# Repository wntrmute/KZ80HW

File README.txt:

WNTRMUTE HARDWARE

This is the electronic design around the KZ80 laptop.

+ KZ80: the actual laptop hardware.
+ tools: support hardware (e.g. programmers).
+ wntrmute.lbr: the WNTRMUTE hardware library.

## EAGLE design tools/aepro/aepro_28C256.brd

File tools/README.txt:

KZ80 tooling
============

This contains support hardware, such as programmers.

+ aepro: AVR EEPROM Programmer
  + 27C512 version
  + 28C256 version
+ busmon: Z80 bus monitor
+ eeprom_adapter: 28-pin wide DIL to ZIF adapter
  + adapter27: for 27C512
  + adapter28: for 28C256
+ m328pgm: ATmega328 programmer for use with AVRISP mkII
+ m1284pgm: ATmega1284 programmer for use with AVRISP mkII
+ RC2014_SIO2: RC2014-compatible SIO/2 board
  + This is built from the standard enhanced-bus SIO/2 board,
    but it only uses the standard (39-pin) RC2014 bus.
  + Note: clock speed is derived from the RC2014 bus, and must
    be 7.4 MHz for 115200 baud operation.
+ SIO2_dev: RC2014 SIO/2 converted to KZ80 interconnect.
+ sercon: standalone serial console

All designs except SIO2_dev are on order but are, as of yet, untested.

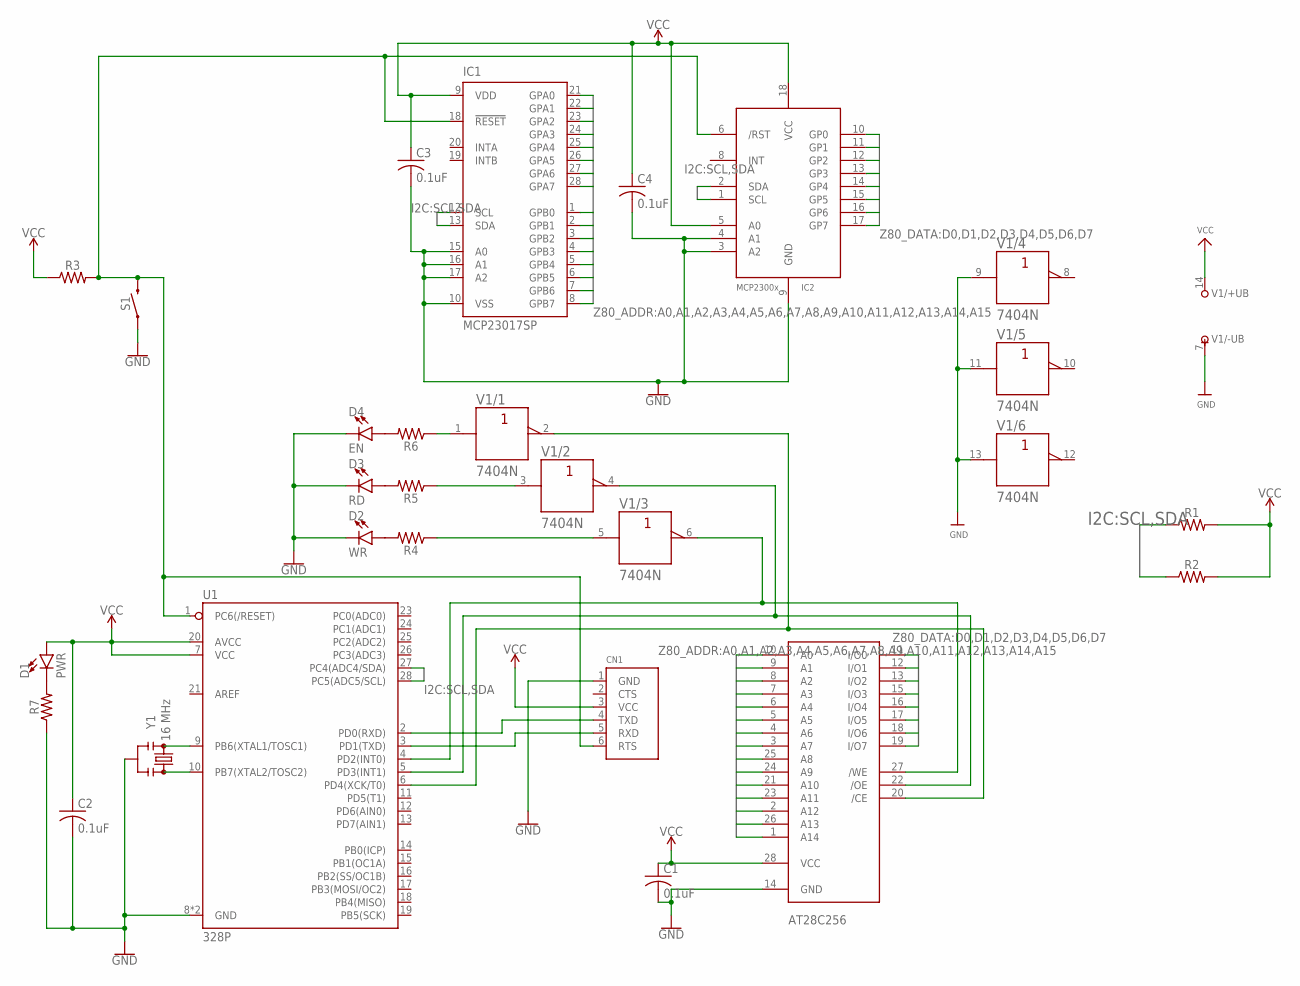
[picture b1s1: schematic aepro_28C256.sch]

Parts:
C1, C2, C3, C4: 0.1uF; C050-024X044
CN1: FTDIUSBCABLE; 1X06_ROUND
D1: PWR; LED_3MM
D2: WR; LED_3MM
D3: RD; LED_3MM
D4: EN; LED_3MM
IC1: MCP23017SP; DIL28-3
IC2: MCP23008/P; DIL18
R1, R2, R3, R4, R5, R6, R7: AXIAL-0.3
S1: MOMENTARY-SWITCH-SPST-PTH-6.0MM; TACTILE_SWITCH_PTH_6.0MM
U1: 328P; DIP28
U$1: AT28C256; DIL28-6-ZIF_SOCKET
V1: 7404N; DIL14
Y1: 16 MHz; RESONATOR-PTH-7.6X3.8

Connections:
A0: IC1.21 (GPA0), U$1.10 (A0)
A1: IC1.22 (GPA1), U$1.9 (A1)
A2: IC1.23 (GPA2), U$1.8 (A2)
A3: IC1.24 (GPA3), U$1.7 (A3)
A4: IC1.25 (GPA4), U$1.6 (A4)
A5: IC1.26 (GPA5), U$1.5 (A5)
A6: IC1.27 (GPA6), U$1.4 (A6)
A7: IC1.28 (GPA7), U$1.3 (A7)
A8: IC1.1 (GPB0), U$1.25 (A8)
A9: IC1.2 (GPB1), U$1.24 (A9)
A10: IC1.3 (GPB2), U$1.21 (A10)
A11: IC1.4 (GPB3), U$1.23 (A11)
A12: IC1.5 (GPB4), U$1.2 (A12)
A13: IC1.6 (GPB5), U$1.26 (A13)
A14: IC1.7 (GPB6), U$1.1 (A14)
A15: IC1.8 (GPB7)
CE: U1.6 (PD4(XCK/T0)), U$1.20 (/CE), V1.2 (Y)
D0: IC2.10 (GP0), U$1.11 (I/O0)
D1: IC2.11 (GP1), U$1.12 (I/O1)
D2: IC2.12 (GP2), U$1.13 (I/O2)
D3: IC2.13 (GP3), U$1.15 (I/O3)
D4: IC2.14 (GP4), U$1.16 (I/O4)
D5: IC2.15 (GP5), U$1.17 (I/O5)
D6: IC2.16 (GP6), U$1.18 (I/O6)
D7: IC2.17 (GP7), U$1.19 (I/O7)
GND: C1.2, C2.2, C3.2, C4.2, CN1.1 (GND), D2.K (C), D3.K (C), D4.K (C), IC1.10 (VSS), IC1.15 (A0), IC1.16 (A1), IC1.17 (A2), IC2.3 (A2), IC2.4 (A1), IC2.9 (GND), R7.P$1 (1), S1.1, U1.8 (GND), U1.22 (GND), U$1.14 (GND), V1.7 (-UB), V1.9 (A), V1.11 (A), V1.13 (A), Y1.2
unnamed: D2.A, R4.P$2 (2)
unnamed: R4.P$1 (1), V1.5 (A)
unnamed: CN1.5 (RXD), U1.3 (PD1(TXD))
unnamed: CN1.6 (RTS), IC1.18 (!RESET), IC2.6 (/RST), R3.P$2 (2), S1.3 (2), U1.1 (PC6(/RESET))
unnamed: D3.A, R5.P$2 (2)
unnamed: D4.A, R6.P$2 (2)
unnamed: D1.K (C), R7.P$2 (2)
unnamed: R5.P$1 (1), V1.3 (A)
unnamed: CN1.4 (TXD), U1.2 (PD0(RXD))
unnamed: U1.9 (PB6(XTAL1/TOSC1)), Y1.1
unnamed: U1.10 (PB7(XTAL2/TOSC2)), Y1.3
unnamed: R6.P$1 (1), V1.1 (A)
OE: U1.5 (PD3(INT1)), U$1.22 (/OE), V1.4 (Y)
SCL: IC1.12 (SCL), IC2.1 (SCL), R1.P$1 (1), U1.28 (PC5(ADC5/SCL))
SDA: IC1.13 (SDA), IC2.2 (SDA), R2.P$1 (1), U1.27 (PC4(ADC4/SDA))
VCC: C1.1, C2.1, C3.1, C4.1, CN1.3 (VCC), D1.A, IC1.9 (VDD), IC2.5 (A0), IC2.18 (VCC), R1.P$2 (2), R2.P$2 (2), R3.P$1 (1), U1.7 (VCC), U1.20 (AVCC), U$1.28 (VCC), V1.14 (+UB)
WE: U1.4 (PD2(INT0)), U$1.27 (/WE), V1.6 (Y)

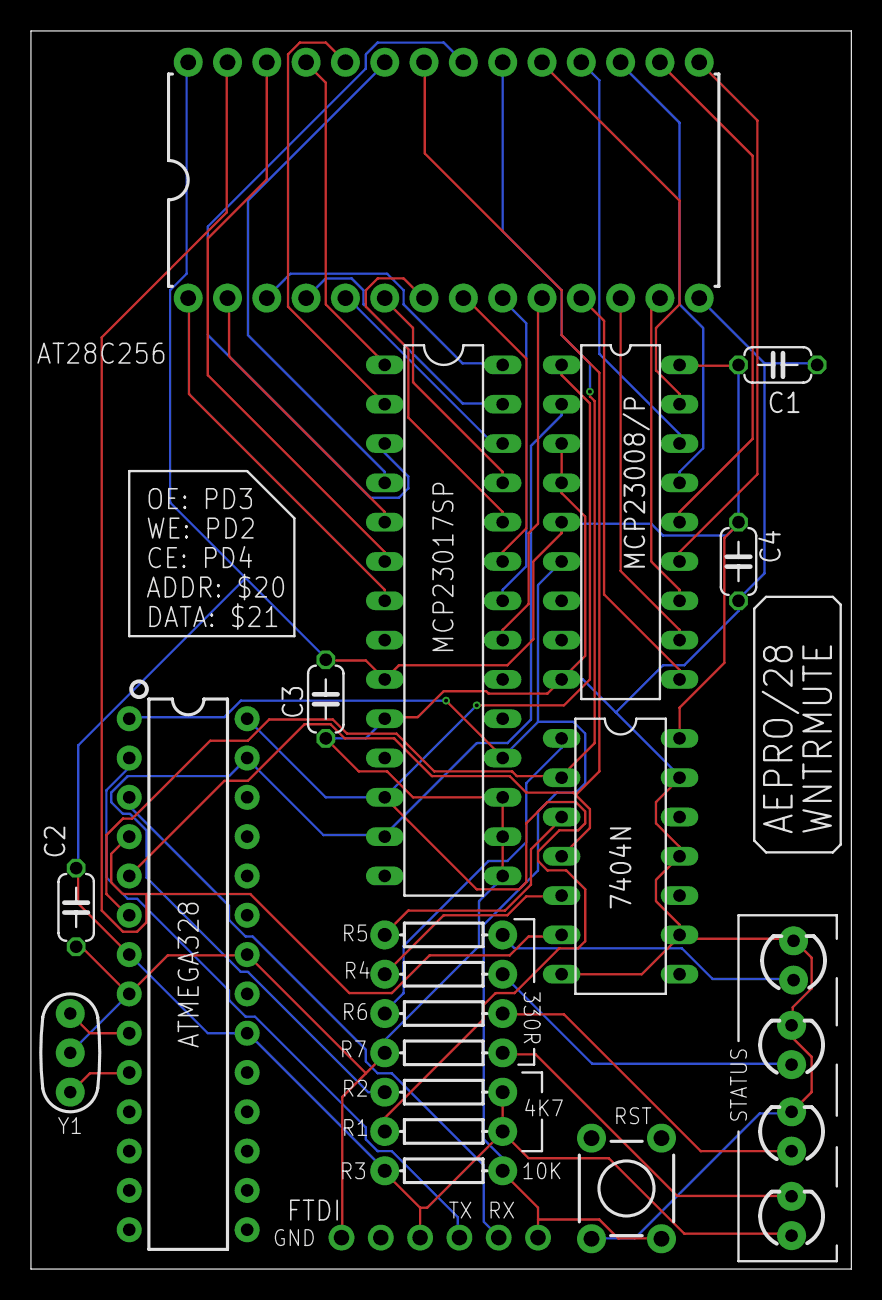
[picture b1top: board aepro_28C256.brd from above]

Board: 2 copper layers, 53.0 x 80.0 mm, 23 parts (0 on the bottom side), 42 nets.

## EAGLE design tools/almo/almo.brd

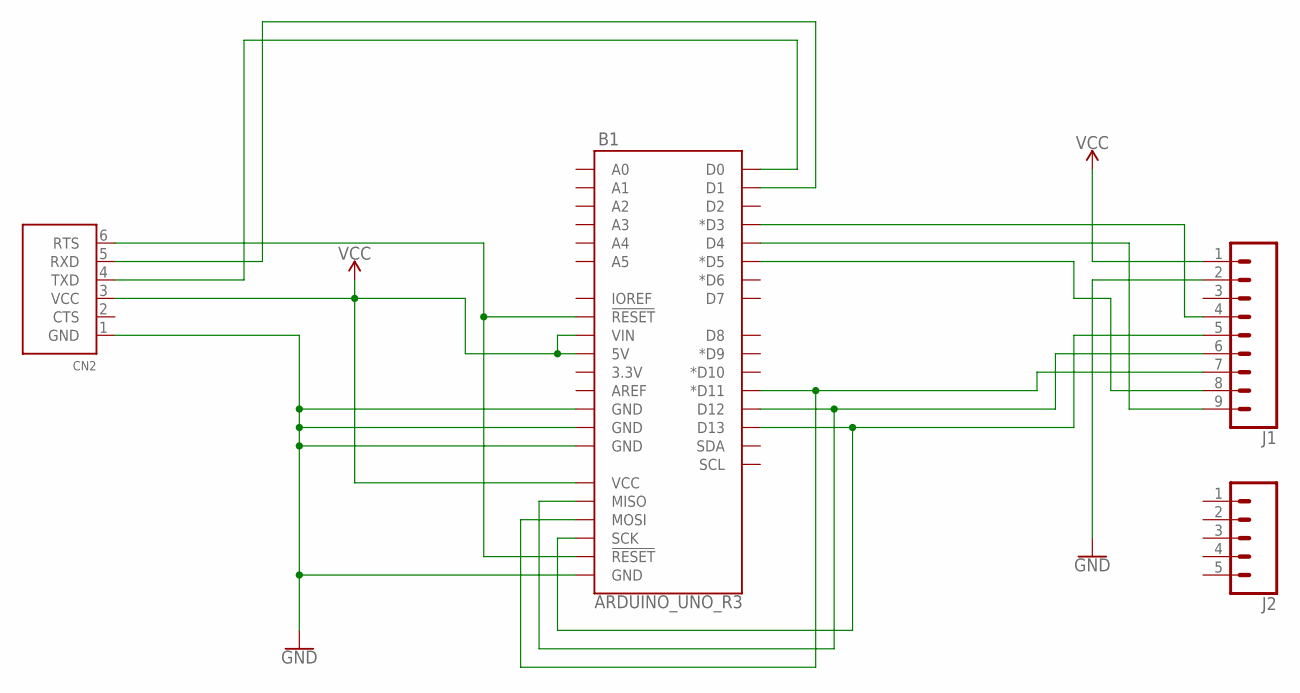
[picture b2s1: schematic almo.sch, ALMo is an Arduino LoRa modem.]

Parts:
B1: ARDUINO_UNO_R3; ARDUINO_R3
CN2: FTDIUSBCABLE; 1X06_ROUND
J1: CONN_09; 1X09
J2: CONN_05; 1X05

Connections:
GND: B1.GND@1 (GND), B1.GND@2 (GND), B1.GND@3 (GND), B1.GND@4 (GND), CN2.1 (GND), J1.2
unnamed: B1.D13, B1.SCK, J1.5
unnamed: B1.RESET@1 (!RESET!), B1.RESET@2 (!RESET!), CN2.6 (RTS)
unnamed: B1.D1, CN2.5 (RXD)
unnamed: B1.D0, CN2.4 (TXD)
unnamed: B1.D12, B1.MISO, J1.6
unnamed: B1.D11 (*D11), B1.MOSI, J1.7
unnamed: B1.D5 (*D5), J1.8
unnamed: B1.D4, J1.9
unnamed: B1.D3 (*D3), J1.4
VCC: B1.5V, B1.VCC, B1.VIN, CN2.3 (VCC), J1.1

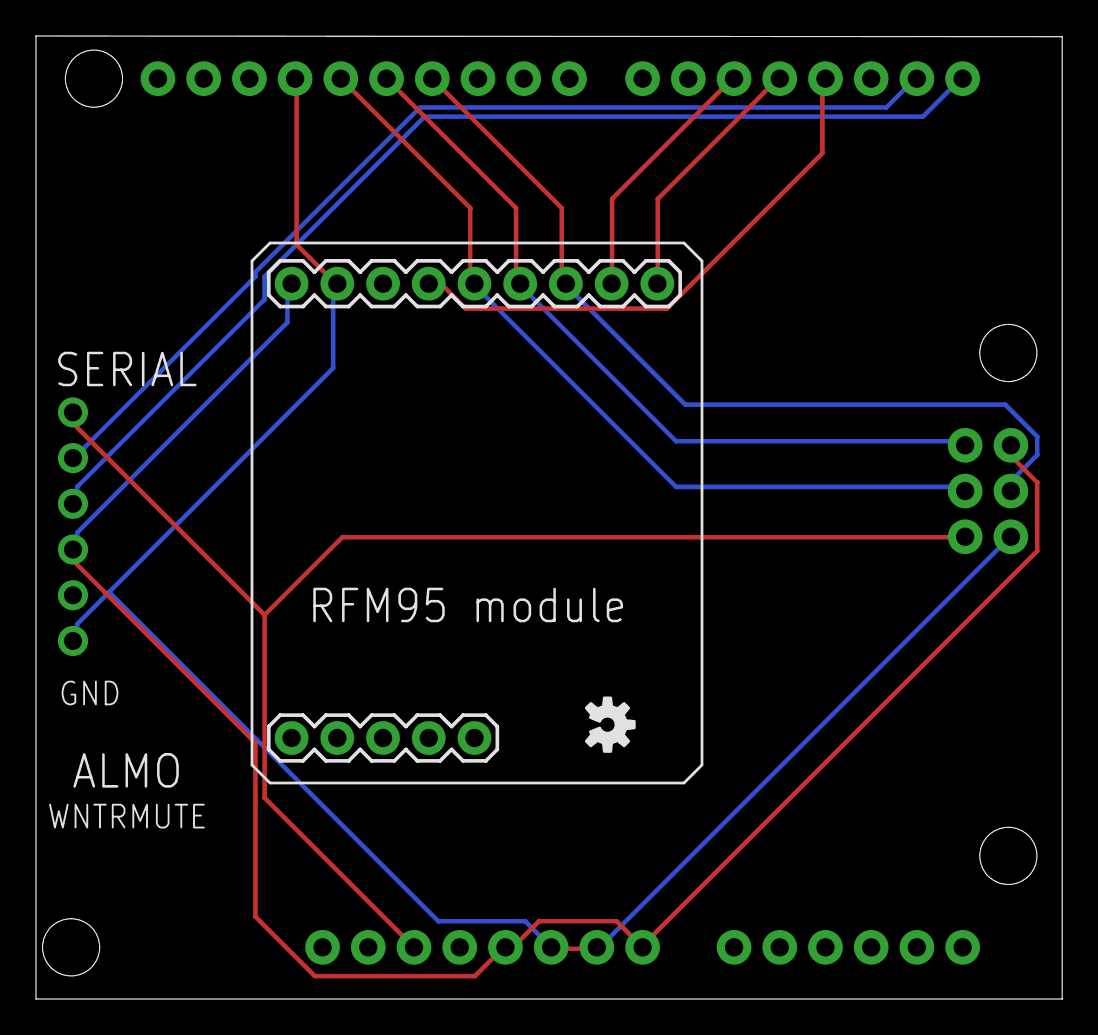
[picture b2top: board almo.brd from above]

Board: 2 copper layers, 57.0 x 53.5 mm, 5 parts (0 on the bottom side), 11 nets.

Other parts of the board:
U$1: OSHW-LOGO-S

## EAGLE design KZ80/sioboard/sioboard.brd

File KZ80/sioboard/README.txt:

SIO/2-based serial console
==========================

This is based on the RC2014 SIO/2 board from Spencer Owens [1]. It's
been adapted specifically to mount on top of the KZ80 mainboard.

|======+=========|
| Port | Address |
|======+=========|
| A/C  |     $80 |
|------+---------|
| A/D  |     $81 |
|------+---------|
| B/C  |     $82 |
|------+---------|
| B/D  |     $83 |
|------+---------|

A = SIO A
B = SIO B
C = CONTROL
D = DATA

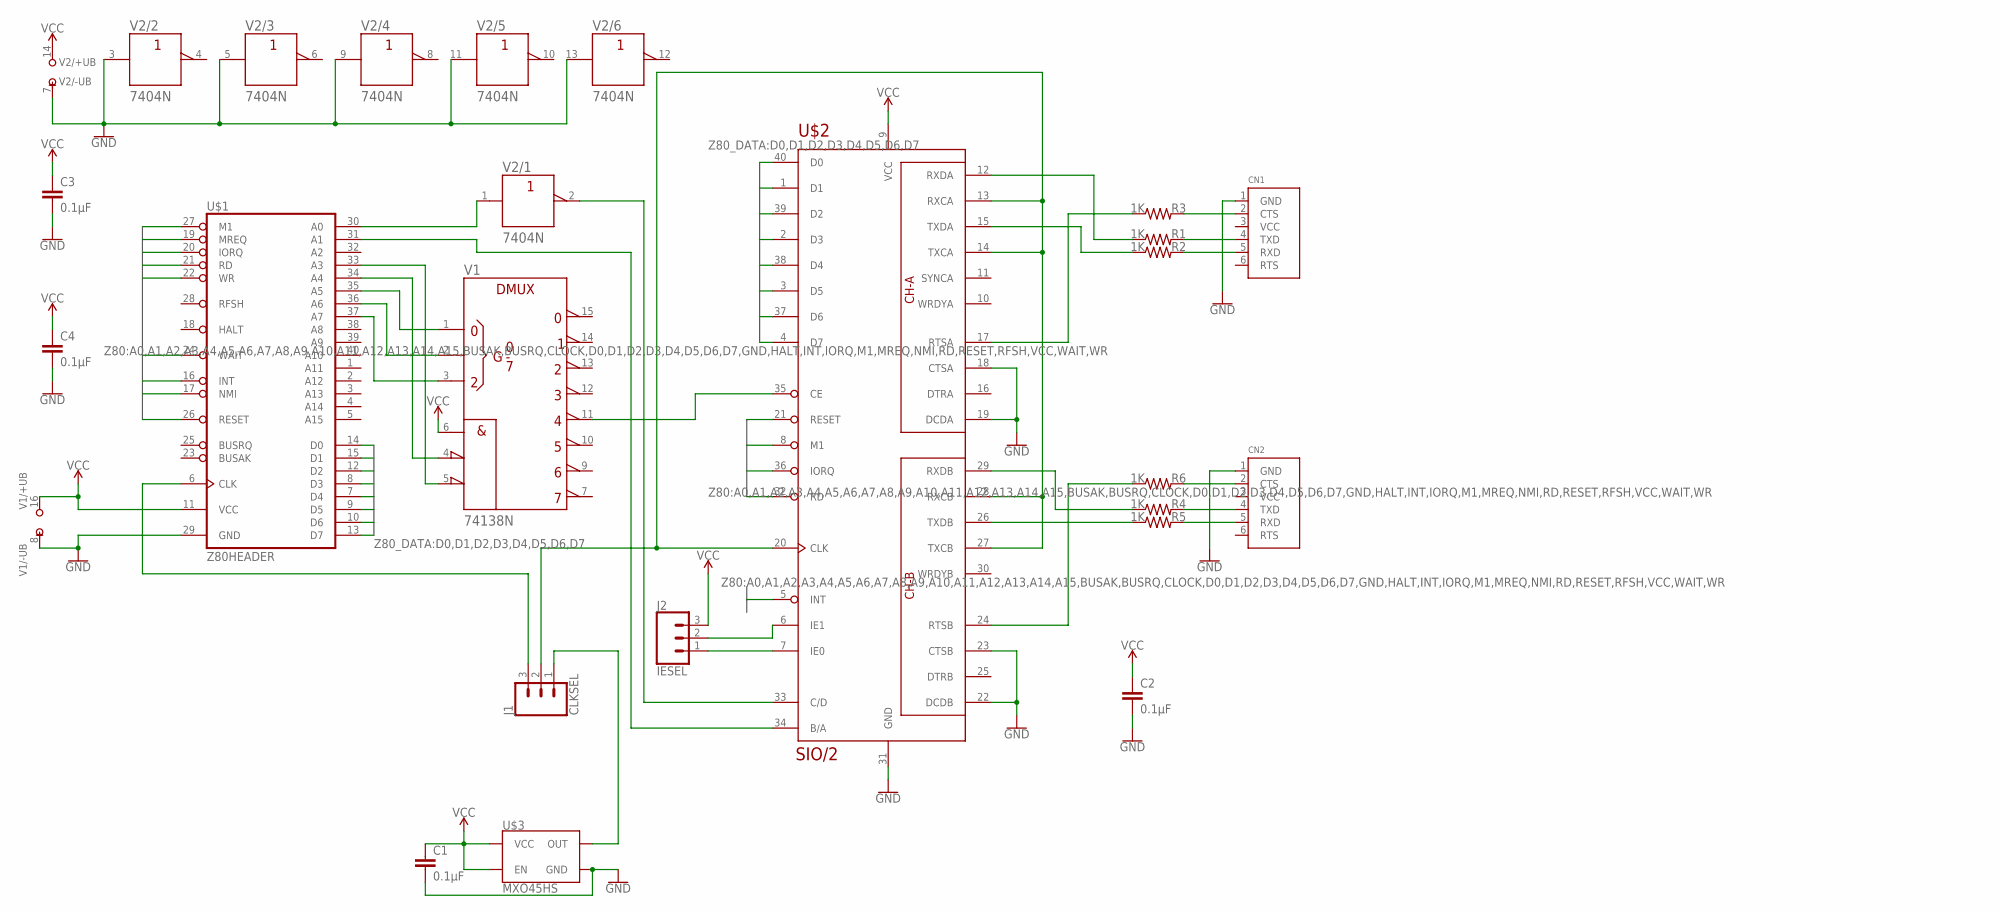
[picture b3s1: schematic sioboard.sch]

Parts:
C1, C2, C3, C4: 0.1µF; C2.5-3
CN1, CN2: FTDIUSBCABLE; 1X06_ROUND
J1: CLKSEL; 1X03
J2: IESEL; 1X03
R1, R2, R3, R4, R5, R6: 1K; AXIAL-0.3
U$1: Z80HEADER; 2X20
U$2: SIO/2; DIL40
U$3: MXO45HS; DIL08-HALF
V1: 74138N; DIL16
V2: 7404N; DIL14

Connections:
D0: U$1.14 (D0), U$2.40 (D0)
D1: U$1.15 (D1), U$2.1 (D1)
D2: U$1.12 (D2), U$2.39 (D2)
D3: U$1.8 (D3), U$2.2 (D3)
D4: U$1.7 (D4), U$2.38 (D4)
D5: U$1.9 (D5), U$2.3 (D5)
D6: U$1.10 (D6), U$2.37 (D6)
D7: U$1.13 (D7), U$2.4 (D7)
GND: C1.2, C2.2, C3.2, C4.2, CN1.1 (GND), CN2.1 (GND), U$1.29 (GND), U$2.18 (CTSA), U$2.19 (DCDA), U$2.22 (DCDB), U$2.23 (CTSB), U$2.31 (GND), U$3.4 (GND), V1.8 (-UB), V2.3 (A), V2.5 (A), V2.7 (-UB), V2.9 (A), V2.11 (A), V2.13 (A)
INT: U$1.16 (INT), U$2.5 (INT)
IORQ: U$1.20 (IORQ), U$2.36 (IORQ)
M1: U$1.27 (M1), U$2.8 (M1)
MREQ: U$1.19 (MREQ)
unnamed: J1.1, U$3.5 (OUT)
unnamed: J1.2, U$2.13 (RXCA), U$2.14 (TXCA), U$2.20 (CLK), U$2.27 (TXCB), U$2.28 (RXCB)
unnamed: J1.3, U$1.6 (CLK)
unnamed: U$1.37 (A7), V1.3 (C)
unnamed: U$1.36 (A6), V1.2 (B)
unnamed: U$1.35 (A5), V1.1 (A)
unnamed: U$1.34 (A4), V1.4 (!G2A)
unnamed: U$1.33 (A3), V1.5 (!G2B)
unnamed: U$2.35 (CE), V1.11 (Y4)
unnamed: U$1.31 (A1), U$2.34 (B/A)
unnamed: U$1.30 (A0), V2.1 (A)
unnamed: U$2.33 (C/D), V2.2 (Y)
unnamed: CN1.2 (CTS), R3.P$2 (2)
unnamed: CN1.4 (TXD), R1.P$2 (2)
unnamed: CN1.5 (RXD), R2.P$2 (2)
unnamed: R2.P$1 (1), U$2.15 (TXDA)
unnamed: R1.P$1 (1), U$2.12 (RXDA)
unnamed: R3.P$1 (1), U$2.17 (RTSA)
unnamed: R4.P$1 (1), U$2.29 (RXDB)
unnamed: R5.P$1 (1), U$2.26 (TXDB)
unnamed: CN2.5 (RXD), R5.P$2 (2)
unnamed: CN2.4 (TXD), R4.P$2 (2)
unnamed: R6.P$1 (1), U$2.24 (RTSB)
unnamed: CN2.2 (CTS), R6.P$2 (2)
unnamed: J2.1, U$2.7 (IE0)
unnamed: J2.2, U$2.6 (IE1)
NMI: U$1.17 (NMI)
RD: U$1.21 (RD), U$2.32 (RD)
RESET: U$1.26 (RESET), U$2.21 (RESET)
VCC: C1.1, C2.1, C3.1, C4.1, J2.3, U$1.11 (VCC), U$2.9 (VCC), U$3.1 (EN), U$3.8 (VCC), V1.6 (G1), V1.16 (+UB), V2.14 (+UB)
WAIT: U$1.24 (WAIT)
WR: U$1.22 (WR)

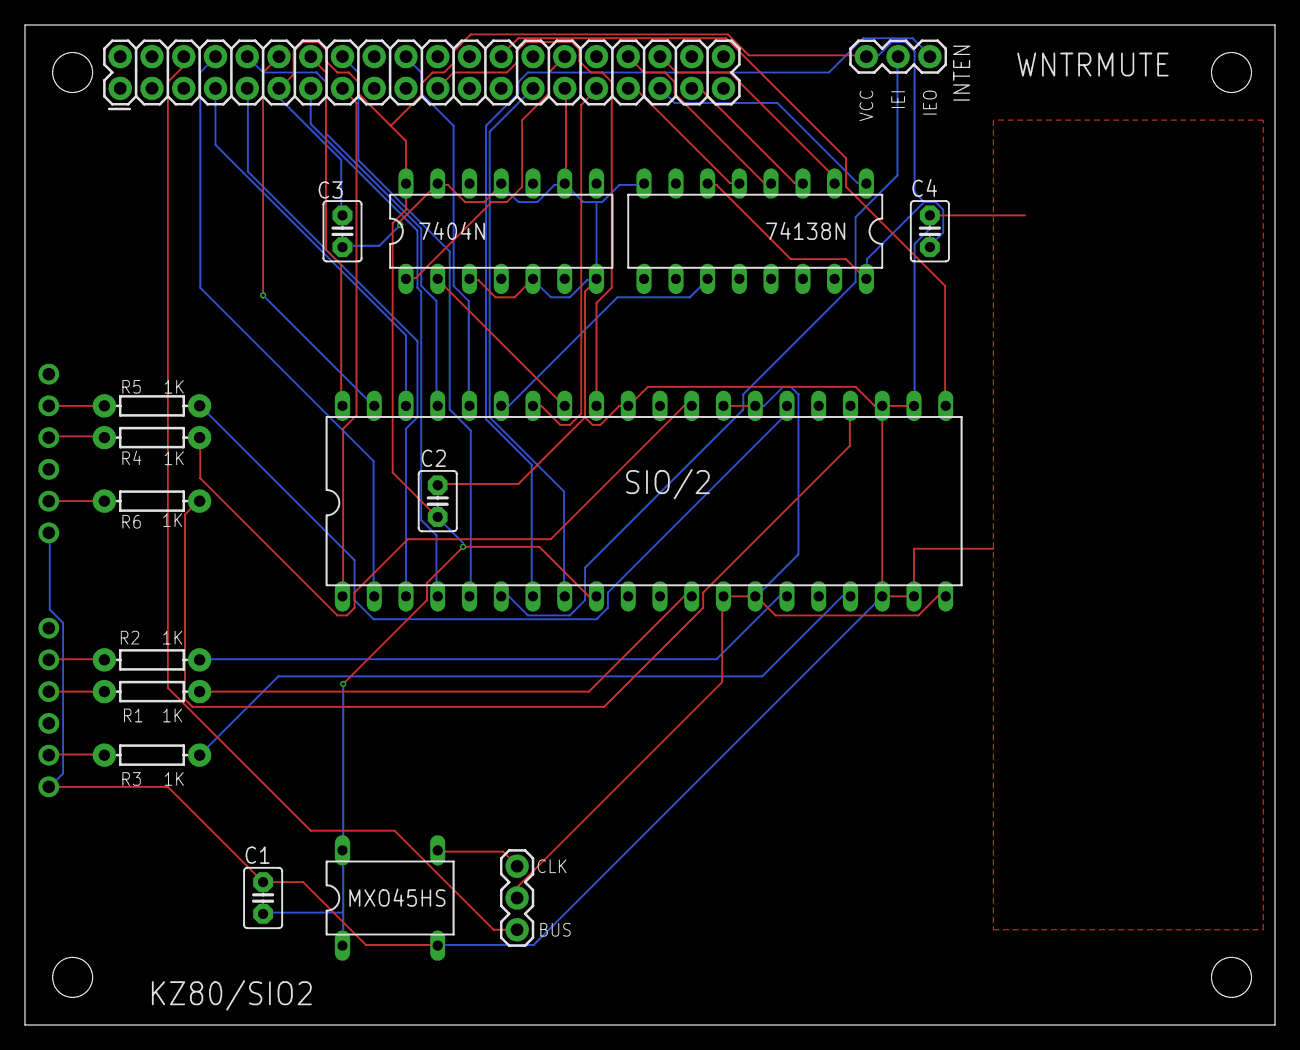
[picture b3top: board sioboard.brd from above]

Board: 2 copper layers, 100.0 x 80.0 mm, 19 parts (0 on the bottom side), 41 nets.

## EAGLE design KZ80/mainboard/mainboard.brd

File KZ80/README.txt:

KZ80 Designs
============

This is the actual KZ80 hardware.

+ backplane: KZ80 interconnect to 5-slot RC2014 bus.
+ mainboard: the current mainboard has 2x CY62256 32K RAM modules and an
  AT28C256 ROM. The ROM is attached to the lower 8K of the address space.
  This design does not feature paging out of the ROM, and as such is
  unsuitable for CP/M.
+ power: the power board provides the clock, a clock+5V connection to
  the mainboard, and a 3.3/5V connection to the I/O board.
+ sioboard: dual serial via a SIO/2.

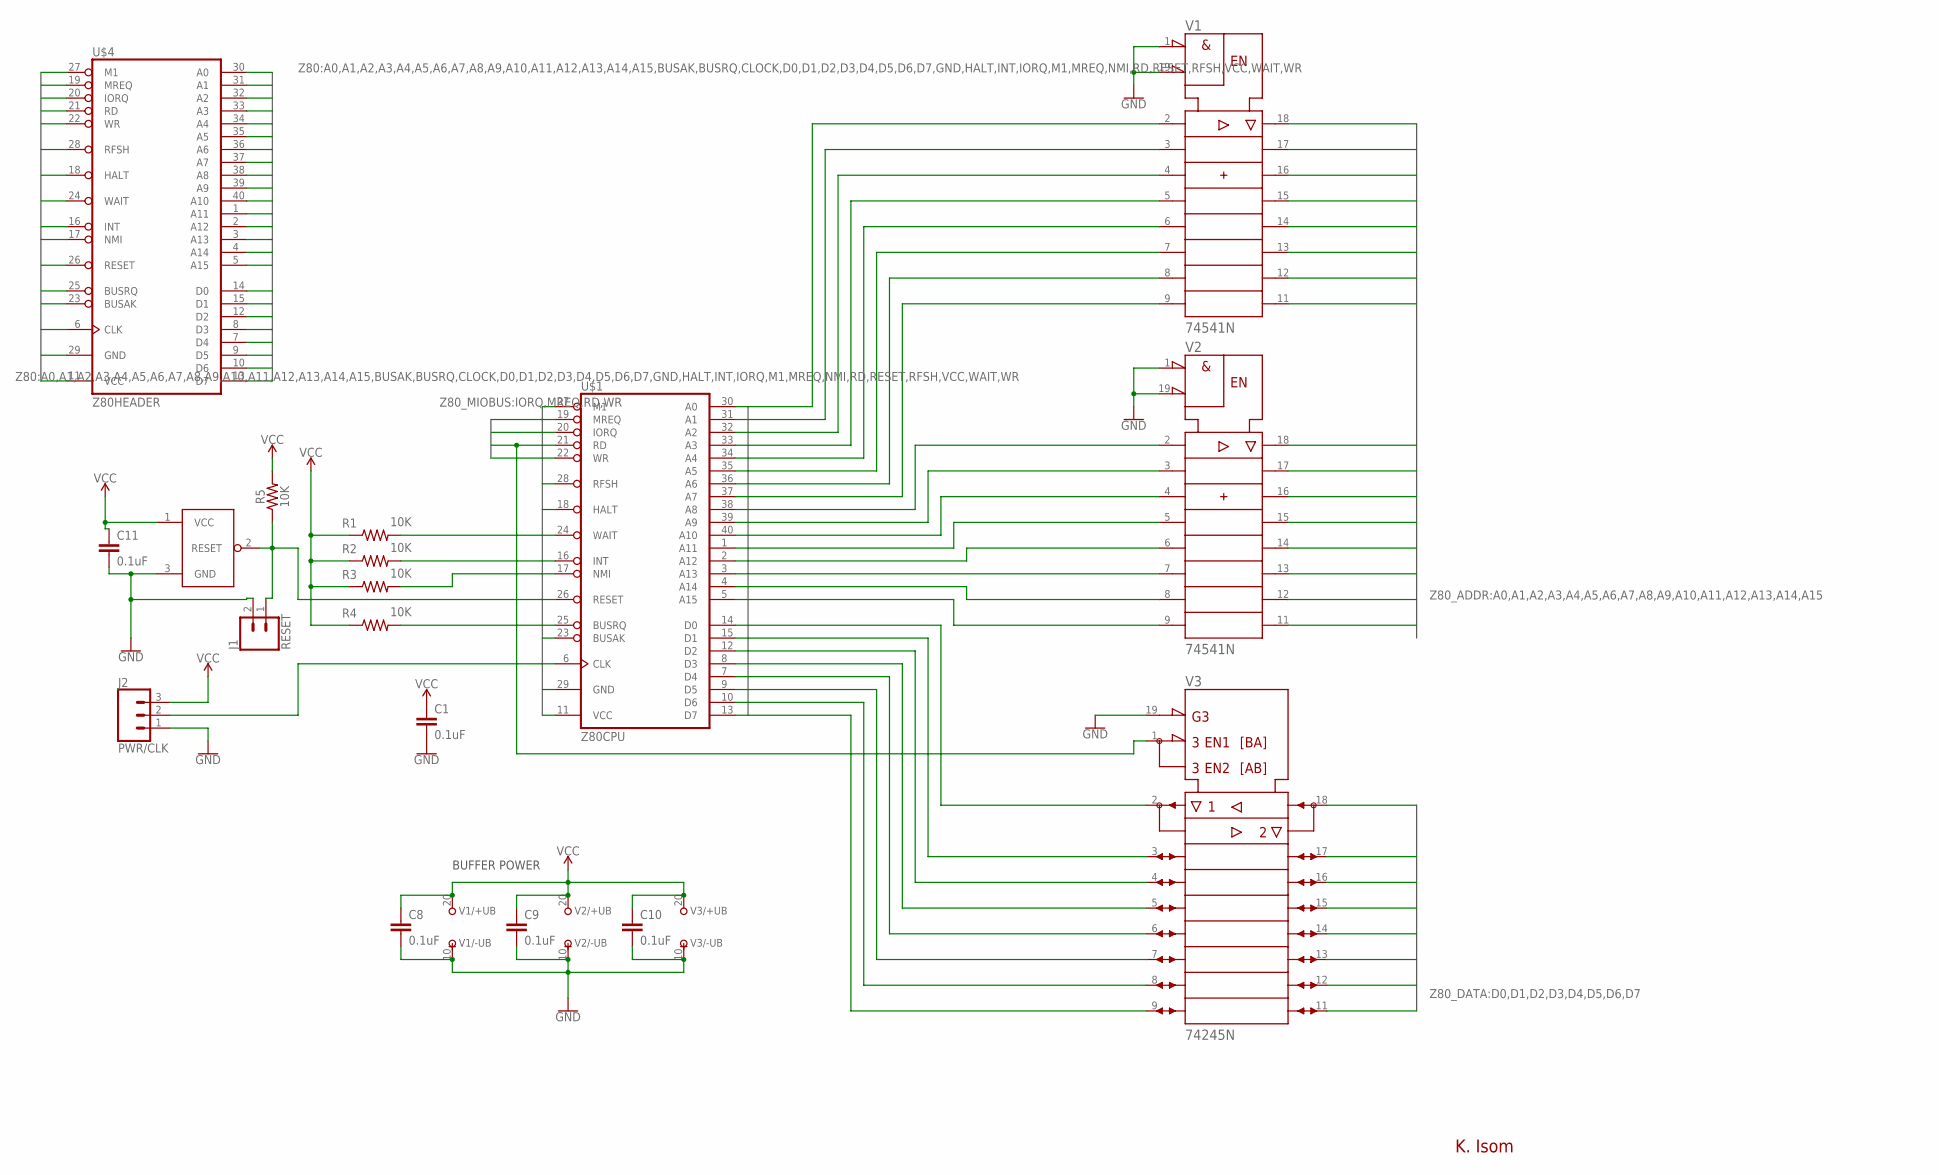
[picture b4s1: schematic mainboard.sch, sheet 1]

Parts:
C1, C8, C9, C10, C11: 0.1uF; C2.5-3
J1: RESET; 1X02
J2: PWR/CLK; SCREWTERMINAL-5MM-3
R1, R2, R3, R4, R5: 10K; AXIAL-0.3
U$1: Z80CPU; DIL40
U$2: MCP120/MCP130; TO-92-AMMO
U$4: Z80HEADER; 2X20
V1, V2: 74541N; DIL20
V3: 74245N; DIL20

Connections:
A0: U$1.30 (A0), U$4.30 (A0), V1.2 (A1), V1.18 (Y1); also elsewhere on the board
A1: U$1.31 (A1), U$4.31 (A1), V1.3 (A2), V1.17 (Y2); also elsewhere on the board
A2: U$1.32 (A2), U$4.32 (A2), V1.4 (A3), V1.16 (Y3); also elsewhere on the board
A3: U$1.33 (A3), U$4.33 (A3), V1.5 (A4), V1.15 (Y4); also elsewhere on the board
A4: U$1.34 (A4), U$4.34 (A4), V1.6 (A5), V1.14 (Y5); also elsewhere on the board
A5: U$1.35 (A5), U$4.35 (A5), V1.7 (A6), V1.13 (Y6); also elsewhere on the board
A6: U$1.36 (A6), U$4.36 (A6), V1.8 (A7), V1.12 (Y7); also elsewhere on the board
A7: U$1.37 (A7), U$4.37 (A7), V1.9 (A8), V1.11 (Y8); also elsewhere on the board
A8: U$1.38 (A8), U$4.38 (A8), V2.2 (A1), V2.18 (Y1); also elsewhere on the board
A9: U$1.39 (A9), U$4.39 (A9), V2.3 (A2), V2.17 (Y2); also elsewhere on the board
A10: U$1.40 (A10), U$4.40 (A10), V2.4 (A3), V2.16 (Y3); also elsewhere on the board
A11: U$1.1 (A11), U$4.1 (A11), V2.5 (A4), V2.15 (Y4); also elsewhere on the board
A12: U$1.2 (A12), U$4.2 (A12), V2.6 (A5), V2.14 (Y5); also elsewhere on the board
A13: U$1.3 (A13), U$4.3 (A13), V2.7 (A6), V2.13 (Y6); also elsewhere on the board
A14: U$1.4 (A14), U$4.4 (A14), V2.8 (A7), V2.12 (Y7); also elsewhere on the board
A15: U$1.5 (A15), U$4.5 (A15), V2.9 (A8), V2.11 (Y8); also elsewhere on the board
BUSAK: U$1.23 (BUSAK), U$4.23 (BUSAK)
BUSRQ: R4.P$2 (2), U$1.25 (BUSRQ), U$4.25 (BUSRQ)
CLOCK: J2.2, U$1.6 (CLK), U$4.6 (CLK)
D0: U$1.14 (D0), U$4.14 (D0), V3.2 (A1), V3.18 (B1); also elsewhere on the board
D1: U$1.15 (D1), U$4.15 (D1), V3.3 (A2), V3.17 (B2); also elsewhere on the board
D2: U$1.12 (D2), U$4.12 (D2), V3.4 (A3), V3.16 (B3); also elsewhere on the board
D3: U$1.8 (D3), U$4.8 (D3), V3.5 (A4), V3.15 (B4); also elsewhere on the board
D4: U$1.7 (D4), U$4.7 (D4), V3.6 (A5), V3.14 (B5); also elsewhere on the board
D5: U$1.9 (D5), U$4.9 (D5), V3.7 (A6), V3.13 (B6); also elsewhere on the board
D6: U$1.10 (D6), U$4.10 (D6), V3.8 (A7), V3.12 (B7); also elsewhere on the board
D7: U$1.13 (D7), U$4.13 (D7), V3.9 (A8), V3.11 (B8); also elsewhere on the board
GND: C1.2, C8.2, C9.2, C10.2, C11.2, J1.2, J2.1, U$1.29 (GND), U$2.3 (GND), U$4.29 (GND), V1.1 (!G1), V1.10 (-UB), V1.19 (!G2), V2.1 (!G1), V2.10 (-UB), V2.19 (!G2), V3.10 (-UB), V3.19 (!G); also elsewhere on the board
HALT: U$1.18 (HALT), U$4.18 (HALT)
INT: R2.P$2 (2), U$1.16 (INT), U$4.16 (INT)
IORQ: U$1.20 (IORQ), U$4.20 (IORQ)
M1: U$1.27 (M1), U$4.27 (M1)
MREQ: U$1.19 (MREQ), U$4.19 (MREQ); also elsewhere on the board
NMI: R3.P$2 (2), U$1.17 (NMI), U$4.17 (NMI)
RD: U$1.21 (RD), U$4.21 (RD), V3.1 (DIR); also elsewhere on the board
RESET: J1.1, R5.P$1 (1), U$1.26 (RESET), U$2.2 (RESET), U$4.26 (RESET)
RFSH: U$1.28 (RFSH), U$4.28 (RFSH)
VCC: C1.1, C8.1, C9.1, C10.1, C11.1, J2.3, R1.P$1 (1), R2.P$1 (1), R3.P$1 (1), R4.P$1 (1), R5.P$2 (2), U$1.11 (VCC), U$2.1 (VCC), U$4.11 (VCC), V1.20 (+UB), V2.20 (+UB), V3.20 (+UB); also elsewhere on the board
WAIT: R1.P$2 (2), U$1.24 (WAIT), U$4.24 (WAIT)
WR: U$1.22 (WR), U$4.22 (WR); also elsewhere on the board

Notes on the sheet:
K. Isom
BUFFER POWER

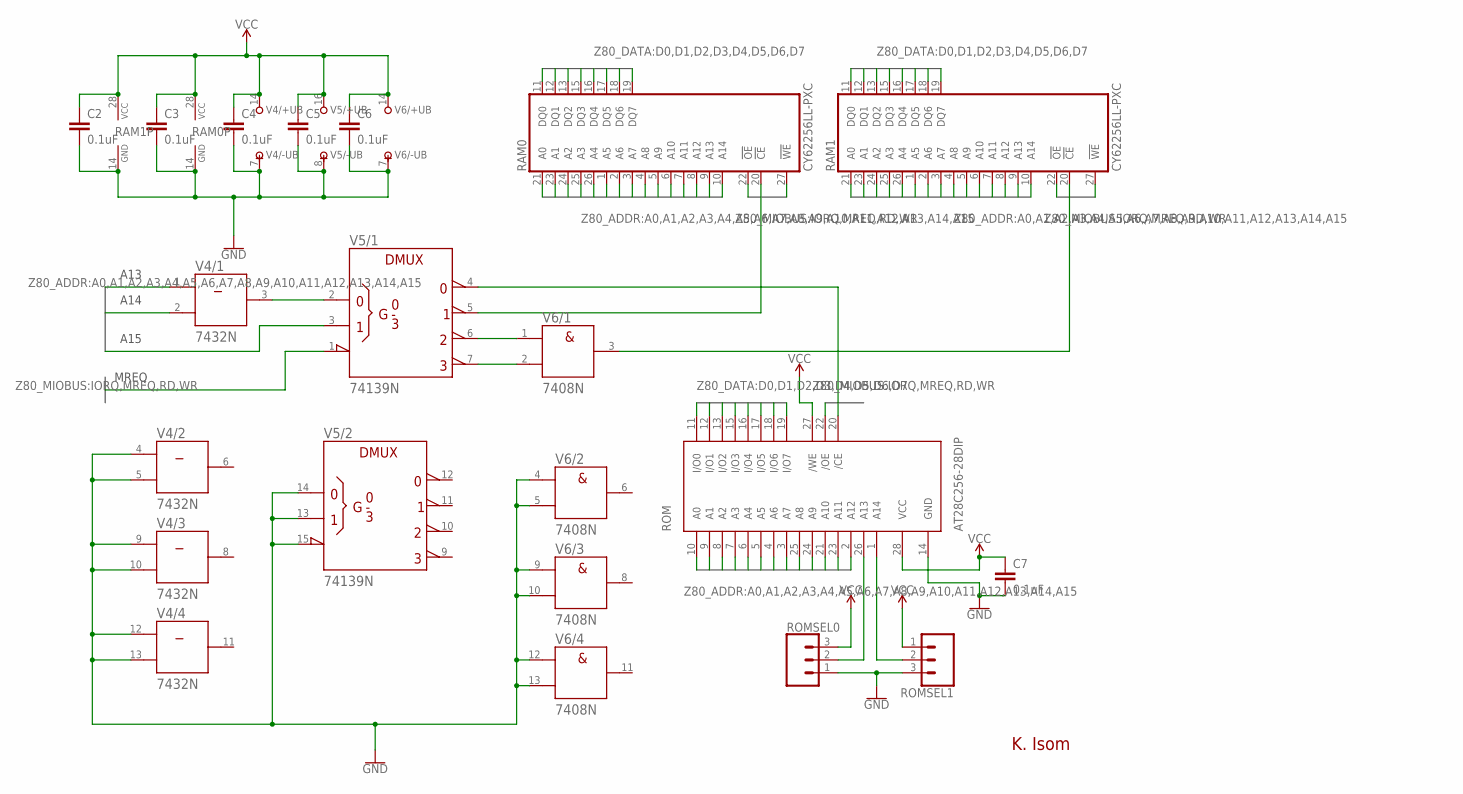
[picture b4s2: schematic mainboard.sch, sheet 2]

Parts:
C2, C3, C4, C5, C6, C7: 0.1uF; C2.5-3
RAM0, RAM1: CY62256LL-PXC; DIL28-6
ROM: AT28C256-28DIP; DIL28-6
ROMSEL0, ROMSEL1: 455-1750-1-ND; 1X03
V4: 7432N; DIL14
V5: 74139N; DIL16
V6: 7408N; DIL14

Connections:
A0: RAM0.21 (A0), RAM1.21 (A0), ROM.10 (A0); also elsewhere on the board
A1: RAM0.23 (A1), RAM1.23 (A1), ROM.9 (A1); also elsewhere on the board
A2: RAM0.24 (A2), RAM1.24 (A2), ROM.8 (A2); also elsewhere on the board
A3: RAM0.25 (A3), RAM1.25 (A3), ROM.7 (A3); also elsewhere on the board
A4: RAM0.26 (A4), RAM1.26 (A4), ROM.6 (A4); also elsewhere on the board
A5: RAM0.1 (A5), RAM1.1 (A5), ROM.5 (A5); also elsewhere on the board
A6: RAM0.2 (A6), RAM1.2 (A6), ROM.4 (A6); also elsewhere on the board
A7: RAM0.3 (A7), RAM1.3 (A7), ROM.3 (A7); also elsewhere on the board
A8: RAM0.4 (A8), RAM1.4 (A8), ROM.25 (A8); also elsewhere on the board
A9: RAM0.5 (A9), RAM1.5 (A9), ROM.24 (A9); also elsewhere on the board
A10: RAM0.6 (A10), RAM1.6 (A10), ROM.21 (A10); also elsewhere on the board
A11: RAM0.7 (A11), RAM1.7 (A11), ROM.23 (A11); also elsewhere on the board
A12: RAM0.8 (A12), RAM1.8 (A12), ROM.2 (A12); also elsewhere on the board
A13: RAM0.9 (A13), RAM1.9 (A13), V4.1 (A); also elsewhere on the board
A14: RAM0.10 (A14), RAM1.10 (A14), V4.2 (B); also elsewhere on the board
A15: V5.3 (B); also elsewhere on the board
D0: RAM0.11 (DQ0), RAM1.11 (DQ0), ROM.11 (I/O0); also elsewhere on the board
D1: RAM0.12 (DQ1), RAM1.12 (DQ1), ROM.12 (I/O1); also elsewhere on the board
D2: RAM0.13 (DQ2), RAM1.13 (DQ2), ROM.13 (I/O2); also elsewhere on the board
D3: RAM0.15 (DQ3), RAM1.15 (DQ3), ROM.15 (I/O3); also elsewhere on the board
D4: RAM0.16 (DQ4), RAM1.16 (DQ4), ROM.16 (I/O4); also elsewhere on the board
D5: RAM0.17 (DQ5), RAM1.17 (DQ5), ROM.17 (I/O5); also elsewhere on the board
D6: RAM0.18 (DQ6), RAM1.18 (DQ6), ROM.18 (I/O6); also elsewhere on the board
D7: RAM0.19 (DQ7), RAM1.19 (DQ7), ROM.19 (I/O7); also elsewhere on the board
GND: C2.2, C3.2, C4.2, C5.2, C6.2, C7.2, RAM0.14 (GND), RAM1.14 (GND), ROM.14 (GND), ROMSEL0.1, ROMSEL1.3, V4.4 (A), V4.5 (B), V4.7 (-UB), V4.9 (A), V4.10 (B), V4.12 (A), V4.13 (B), V5.8 (-UB), V5.13 (B), V5.14 (A), V5.15 (!G), V6.4 (A), V6.5 (B), V6.7 (-UB), V6.9 (A), V6.10 (B), V6.12 (A), V6.13 (B); also elsewhere on the board
MREQ: V5.1 (!G); also elsewhere on the board
unnamed: ROM.26 (A13), ROMSEL0.2
unnamed: V4.3 (Y), V5.2 (A)
unnamed: V5.6 (Y2), V6.1 (A)
unnamed: V5.7 (Y3), V6.2 (B)
unnamed: RAM0.20 (!CE), V5.5 (Y1)
unnamed: ROM.20 (/CE), V5.4 (Y0)
unnamed: RAM1.20 (!CE), V6.3 (Y)
unnamed: ROM.1 (A14), ROMSEL1.2
RD: RAM0.22 (!OE), RAM1.22 (!OE), ROM.22 (/OE); also elsewhere on the board
VCC: C2.1, C3.1, C4.1, C5.1, C6.1, C7.1, RAM0.28 (VCC), RAM1.28 (VCC), ROM.27 (/WE), ROM.28 (VCC), ROMSEL0.3, ROMSEL1.1, V4.14 (+UB), V5.16 (+UB), V6.14 (+UB); also elsewhere on the board
WR: RAM0.27 (!WE), RAM1.27 (!WE); also elsewhere on the board

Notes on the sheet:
A13
A14
A15
MREQ
K. Isom

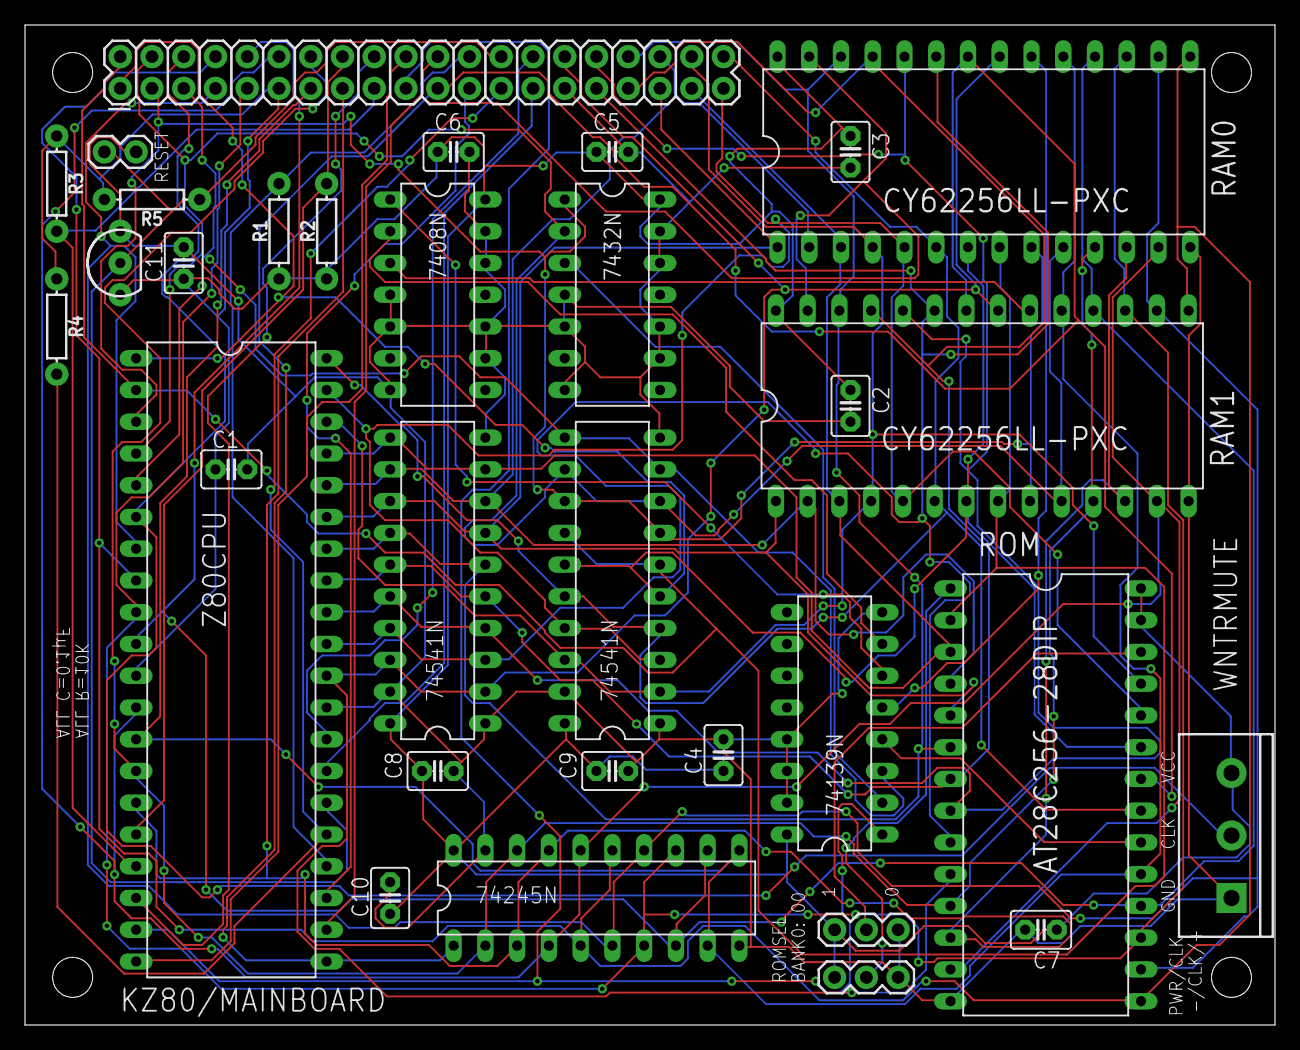
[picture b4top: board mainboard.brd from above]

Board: 2 copper layers, 100.0 x 80.0 mm, 32 parts (0 on the bottom side), 48 nets.

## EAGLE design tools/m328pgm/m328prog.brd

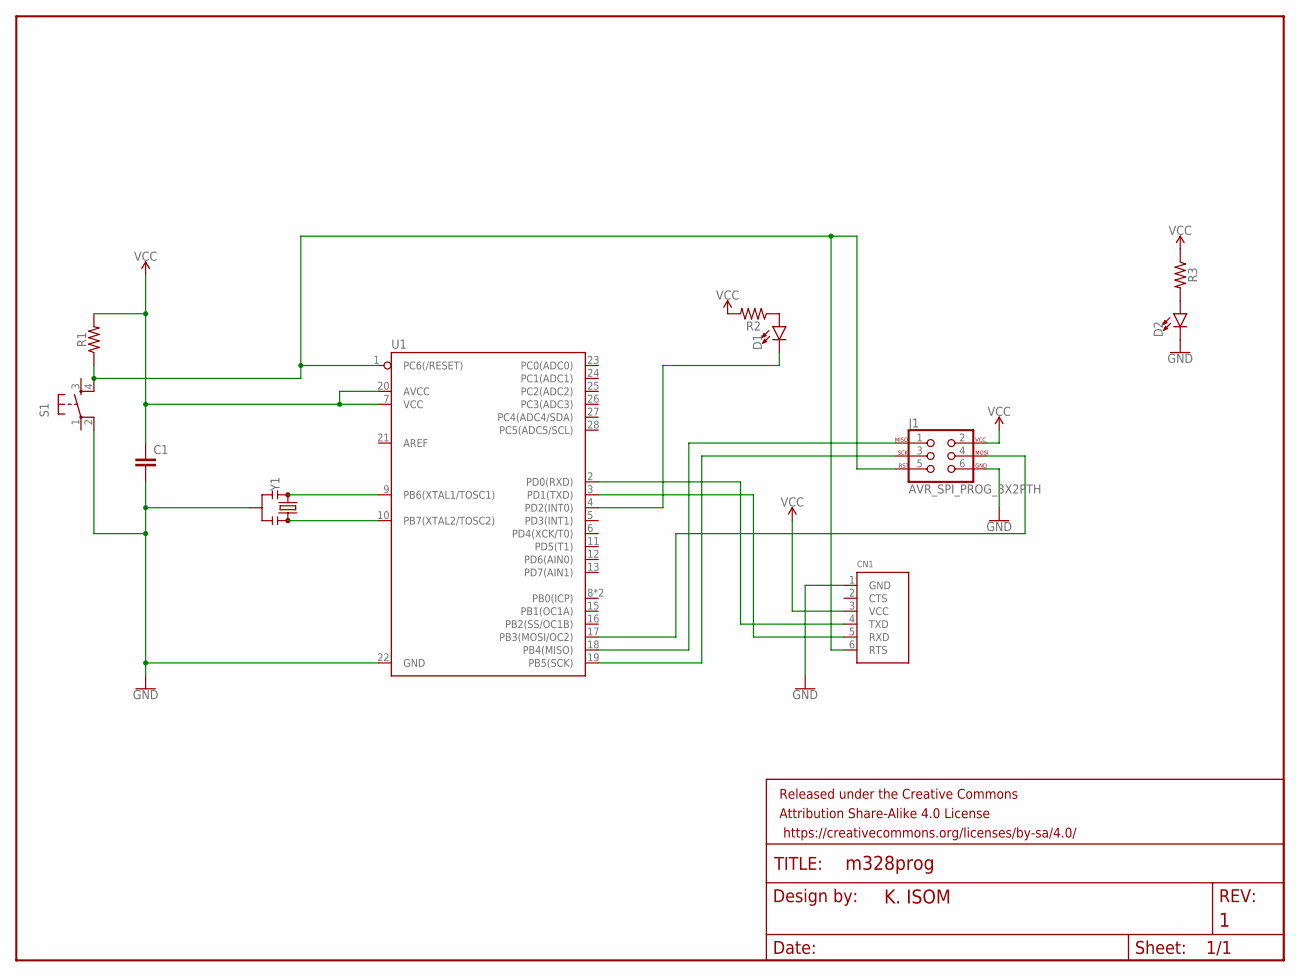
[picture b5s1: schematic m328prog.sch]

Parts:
C1: C2,5-3; C2.5-3
CN1: FTDIUSBCABLE; 1X06_ROUND
D1, D2: LED3MM; LED_3MM
FRAME1: FRAME-LETTER; CREATIVE_COMMONS
J1: AVR_SPI_PROG_3X2PTH; 2X3
R1, R2, R3: AXIAL-0.3
S1: TAC_SWITCHPTH; TACTILE-PTH
U1: ATMEGA328P; DIL28-3-ZIF_SOCKET
Y1: RESONATORPTH-7.6X3.8; RESONATOR-PTH-7.6X3.8

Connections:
GND: C1.2, CN1.1 (GND), D2.K (C), J1.6, S1.2, U1.22 (GND), Y1.2
unnamed: U1.9 (PB6(XTAL1/TOSC1)), Y1.1
unnamed: U1.10 (PB7(XTAL2/TOSC2)), Y1.3
unnamed: J1.4, U1.17 (PB3(MOSI/OC2))
unnamed: CN1.6 (RTS), J1.5, R1.P$1 (1), S1.4, U1.1 (PC6(/RESET))
unnamed: J1.1, U1.18 (PB4(MISO))
unnamed: J1.3, U1.19 (PB5(SCK))
unnamed: D1.K (C), U1.4 (PD2(INT0))
unnamed: D1.A, R2.P$1 (1)
unnamed: CN1.5 (RXD), U1.3 (PD1(TXD))
unnamed: CN1.4 (TXD), U1.2 (PD0(RXD))
unnamed: D2.A, R3.P$2 (2)
VCC: C1.1, CN1.3 (VCC), J1.2, R1.P$2 (2), R2.P$2 (2), R3.P$1 (1), U1.7 (VCC), U1.20 (AVCC)

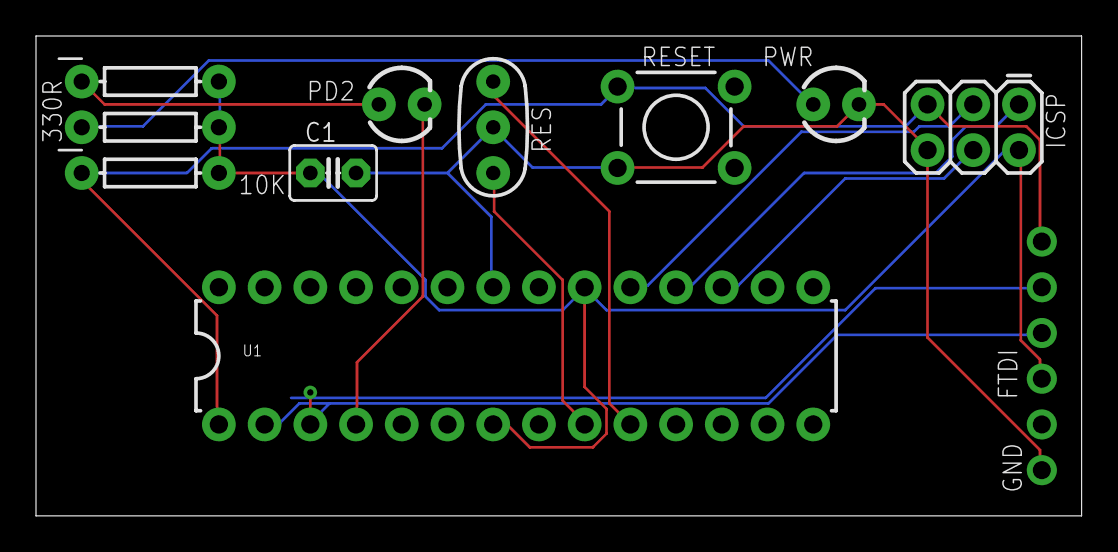
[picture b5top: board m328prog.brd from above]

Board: 2 copper layers, 58.1 x 26.7 mm, 12 parts (0 on the bottom side), 13 nets.

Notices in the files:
parts and their libraries:
microbuilder: This work is placed in the public domain, and may be freely used for commercial and non-commercial work with the following conditions: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
SparkFun-Connectors: Licensing: Creative Commons ShareAlike 4.0 International - https://creativecommons.org/licenses/by-sa/4.0
